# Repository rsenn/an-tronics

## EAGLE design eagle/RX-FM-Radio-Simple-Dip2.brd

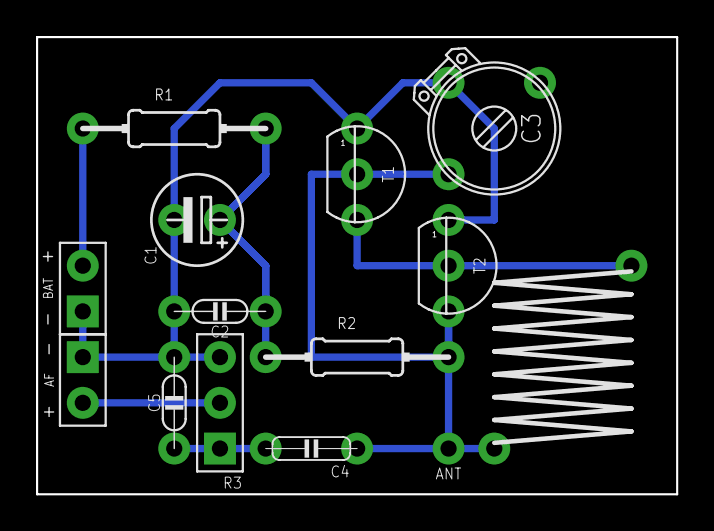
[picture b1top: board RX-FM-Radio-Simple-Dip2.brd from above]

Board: 2 copper layers, 35.6 x 25.4 mm, 14 parts (0 on the bottom side), 7 nets.

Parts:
AF: SPAD+-+-; SPAD+-
ANT: ANT; SPAD
BAT: VCC_GNDL; SPAD-+
C1: 100µF; E2,5-5/V
C2: 100nF; C050-020X036/V
C3: 2 - 20pF; TRIM-2222-808
C4: 220nF; C050-020X044
C5: 2.2nF; C050-020X036/V
L1: 0.2µH; L-10/10Y
R1: 1kΩ; 0204/10
R2: 10kΩ; 0204/10
R3: 10kΩ; CONN-3P
T1, T2: 2N2222; TO92

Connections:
GND: AF.1, BAT.1, C1.-, C2.2, C3.2, C5.2, R3.3, T1.1, T2.1
unnamed: ANT.1, C3.3, C4.1, L1.P$1, R2.2, T1.2, T2.3
unnamed: C1.+, C2.1, R1.2, R2.1
unnamed: C4.2, C5.1, R3.1
unnamed: L1.P$2, T1.3, T2.2
unnamed: AF.2, R3.2
VCC: BAT.2, R1.1

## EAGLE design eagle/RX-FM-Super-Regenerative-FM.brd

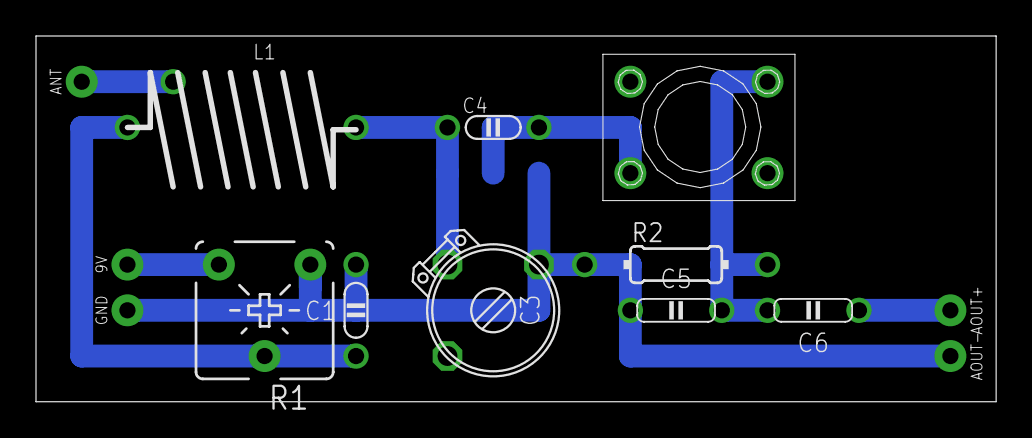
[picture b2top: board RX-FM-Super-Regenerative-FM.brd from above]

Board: 2 copper layers, 53.3 x 20.3 mm, 14 parts (0 on the bottom side), 8 nets.

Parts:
9V: SPAD
ANT: ANT; SPAD
AOUT+: SPAD
AOUT-: SPAD
C1: 1n; C050-020X036/V
C3: 15p; TRIM-2222-808
C4: 4.7pF; C050-020X036
C5: 4.7n; C050-020X044
C6: 100n; C050-020X044
GND: SPAD
L1: 0.22μH; L-08/12-X-TAP1
L2: 3.3μH; L-BODY
R1: 1kΩ; POT-V
R2: 10kΩ; 0204/10

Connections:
GND: AOUT-.1, C1.2, C3.1, C5.2, GND.1, R1.A, R2.1
unnamed: 9V.1, R1.E
unnamed: C3.2, C4.1, L1.2
unnamed: C1.1, L1.1, R1.S
unnamed: ANT.1, L1.3
unnamed: C4.2, L2.3
unnamed: C5.1, C6.1, L2.2, R2.2
unnamed: AOUT+.1, C6.2

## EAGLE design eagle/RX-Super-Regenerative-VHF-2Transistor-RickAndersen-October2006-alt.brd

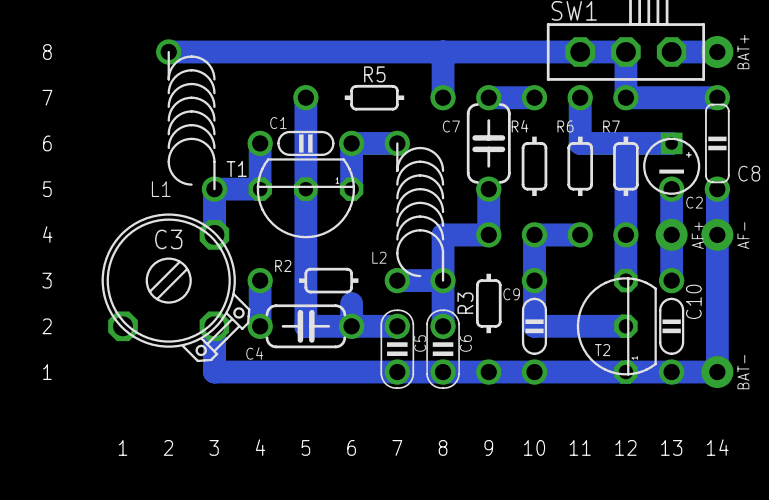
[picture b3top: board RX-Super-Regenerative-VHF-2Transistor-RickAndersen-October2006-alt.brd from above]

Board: 2 copper layers, 25 parts (0 on the bottom side), 12 nets.

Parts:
AF+: SPAD
AF-: SPAD
BAT+: SPAD
BAT-: SPAD
C1: 7pF; C050-020X036
C2: 2.2μF; E2,5-3
C3: 15pF; TRIM-2222-808
C4: 470nF; C050-024X044/V
C5, C6: 1nF; C025-020X036
C7: 470n; C050-024X044/V
C8: 100nF; C050-020X044/V
C9: 10nF; C050-020X036/V
C10: 47nF; C050-020X036
L1, L2: 6; L-04/8V
R2: 12kΩ; 0202/7
R3: 10kΩ; 0202/7
R4: 22kΩ; 0202/7-V
R5: 330kΩ; 0202/7
R6: 220kΩ; 0202/7-V
R7: 4.7kΩ; 0202/7-V
SW1: SL-SW-1P-2T-H; SLSW-1P2T-H
T1, T2: 2N3904; TO92

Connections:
GND: AF-.1, BAT-.1, C3.2, C5.2, C6.2, C8.2, C9.2, C10.2, R3.2, T2.1
unnamed: C1.2, C3.3, L1.1, T1.3
unnamed: C1.1, L2.2, T1.1
unnamed: C7.1, R4.1
unnamed: C4.2, C5.1, R5.2, T1.2
unnamed: C2.+, R6.2, R7.1, T2.3
unnamed: C6.1, C7.2, L2.1, R2.2, R3.1
unnamed: C4.1, R2.1
unnamed: BAT+.1, SW1.1
unnamed: C9.1, R4.2, R6.1, T2.2
unnamed: AF+.1, C2.-, C10.1
VCC: C8.1, L1.2, R5.1, R7.2, SW1.3

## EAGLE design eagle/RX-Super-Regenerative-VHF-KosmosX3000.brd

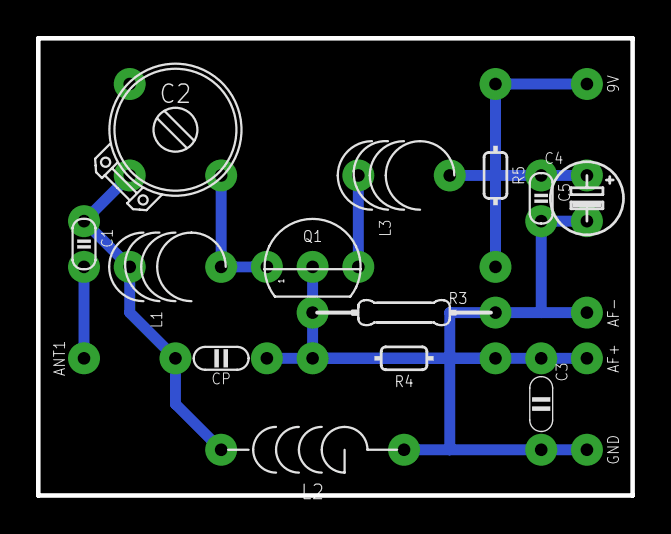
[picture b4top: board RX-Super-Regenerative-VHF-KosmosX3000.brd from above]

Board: 2 copper layers, 33.0 x 25.4 mm, 18 parts (0 on the bottom side), 9 nets.

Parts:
9V: SPAD; SPAD@1
AF+: SPAD; SPAD@1
AF-: SPAD; SPAD@1
ANT1: ANT; SPAD
C1: 15p; C025-015X024
C2: 15p; TRIM-2222-808
C3: 6.8n; C050-020X036
C4: 100u; E2.5-4/V
C5: 100n; C025-015X024
CP: 4.7n; C050-020X036/V
GND: SPAD; SPAD@1
L1: L04/7; L-04-5/6V-C
L2: L-03/10
L3: 4 turns; L-04-5/6V-C
Q1: BF256B; TO92
R3: 3.3kΩ; 0204/10
R4: 10kΩ; 0202/10
R5: 150Ω; 0202/10

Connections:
GND: AF-.1, C3.2, C4.-, C5.2, GND.1, L2.2, R3.2
unnamed: CP.1, Q1.2, R3.1, R4.1
unnamed: AF+.1, C3.1, R4.2
unnamed: ANT1.1, C1.2
unnamed: C4.+, C5.1, L3.1, R5.1
unnamed: C2.3, L1.1, Q1.1
unnamed: C1.1, C2.2, CP.2, L1.2, L2.1
unnamed: L3.2, Q1.3
unnamed: 9V.1, R5.2

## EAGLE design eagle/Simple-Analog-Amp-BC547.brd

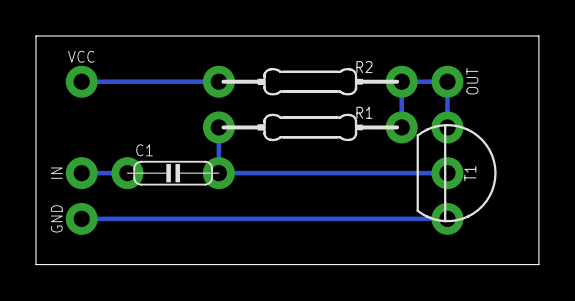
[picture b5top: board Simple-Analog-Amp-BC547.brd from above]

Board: 2 copper layers, 27.9 x 12.7 mm, 8 parts (0 on the bottom side), 5 nets.

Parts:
C1: 100n; C050-020X044
GND: VPORT; SPAD
IN: HPORT; SPAD
OUT: HPORT; SPAD
R1: 470kΩ; 0204/10
R2: 1kΩ; 0204/10
T1: BC547; TO92-CBE
VCC: VPORT; SPAD

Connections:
unnamed: C1.2, R1.1, T1.2
unnamed: OUT.1, R1.2, R2.2, T1.1
unnamed: C1.1, IN.1
unnamed: GND.1, T1.3
unnamed: R2.1, VCC.1

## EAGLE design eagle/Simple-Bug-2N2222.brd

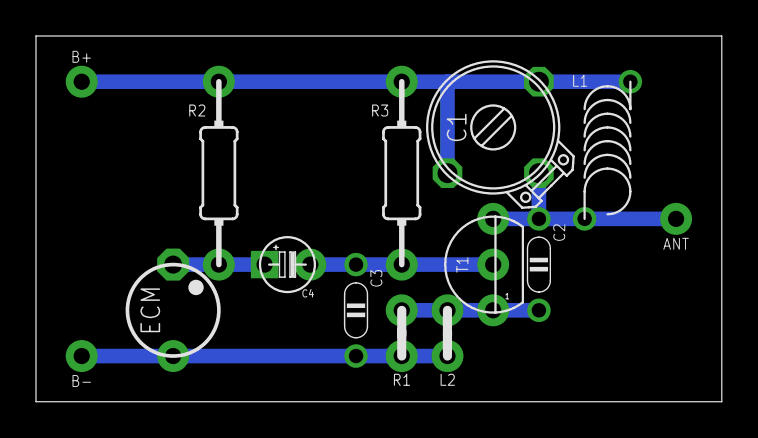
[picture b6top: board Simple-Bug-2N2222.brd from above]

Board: 2 copper layers, 38.1 x 20.3 mm, 14 parts (0 on the bottom side), 6 nets.

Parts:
ANT: ANT; SPAD
B+: HPORT; SPAD
B-: HPORT; SPAD
C1: 2-20pF; TRIM-2222-808
C2: 5pF; C050-020X036
C3: 1nF; C050-020X036
C4: 1μF; E2,5-3
ECM: ECM-5
L1: 200nH; L-04/7V-X
L2: 1μH; 0204/2V
R1: 4.7Ω; 0204/2V
R2: 4.7kΩ; 0204/10-V
R3: 10kΩ; 0204/10-V
T1: 2N2222; TO92

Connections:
+: B+.1, C1.1, C1.3, L1.2, R2.1, R3.1
-: B-.1, C3.2, ECM.2, L2.1, R1.1
AF: C4.+, ECM.1, R2.2
BIAS: C2.2, L2.2, R1.2, T1.1
MOD: C3.1, C4.-, R3.2, T1.2
RF: ANT.1, C1.2, C2.1, L1.1, T1.3

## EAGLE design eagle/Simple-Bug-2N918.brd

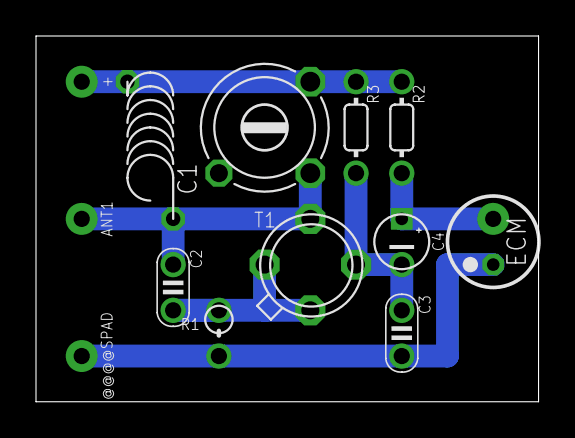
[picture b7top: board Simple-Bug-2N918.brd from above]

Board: 2 copper layers, 27.9 x 20.3 mm, 13 parts (0 on the bottom side), 6 nets.

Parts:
+: SPAD
@@@@SPAD: SPAD
ANT1: ANT; SPAD
C1: C-TR-PH20127-45-2P23; TRIM808-45
C2: 4.7pF; C025-020X036
C3: 1nF; C025-020X036
C4: E2,5-3
ECM: ECM-5
L1: 1μH; L-04/7
R1: 0202V
R2: 22kΩ; 0202/5
R3: 47kΩ; 0202/5
T1: 2N918; TO72-A45

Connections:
+UB: +.1, C1.1, L1.1, R2.1, R3.1
GND: C3.2, ECM.1, R1.1
unnamed: ANT1.1, C1.2, C2.1, L1.2, T1.3
unnamed: C2.2, R1.2, T1.1
unnamed: C3.1, C4.-, R3.2, T1.2
unnamed: C4.+, ECM.2, R2.2
